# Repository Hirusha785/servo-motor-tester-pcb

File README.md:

# 🔧 Servo Motor Tester PCB

A compact PCB design for testing and controlling hobby servo motors using a 555 timer-based PWM signal generator. This project is designed for electronics learning, servo testing, prototyping, and basic embedded hardware experimentation.

---

## 📌 Project Overview

The **Servo Motor Tester PCB** allows users to generate a variable PWM signal to test standard servo motors without needing a microcontroller such as Arduino or ESP32. The circuit is based on the **NE555 timer IC**, with a potentiometer used to adjust the servo position by varying the pulse width.

This PCB is useful for checking servo motor movement, validating servo wiring, testing power connections, and learning basic PWM control concepts.

---

## ✨ Features

- 🔧 NE555-based PWM signal generation  
- 🎚️ Potentiometer control for servo position adjustment  
- 🔌 Dedicated 3-pin servo output connector  
- ⚡ 6V DC input supply connector  
- 💡 Power indicator LED  
- 🧩 Compact PCB layout  
- 🛠️ Beginner-friendly through-hole component design  
- 📐 Designed using KiCad  

---

## 🧠 How It Works

Servo motors are controlled using a PWM signal. A typical hobby servo expects a pulse every 20 ms, where the pulse width determines the motor position.

Typical servo control range:

| Pulse Width | Servo Position |
|------------|----------------|
| ~1.0 ms | 0° |
| ~1.5 ms | 90° |
| ~2.0 ms | 180° |

In this circuit, the **NE555 timer** works as an adjustable pulse generator. The potentiometer changes the timing resistance, which changes the output pulse width. This output signal is sent to the servo motor through the signal pin.

---

## 🧾 Components Used

| Reference | Component | Value / Type |
|----------|-----------|--------------|
| U1 | Timer IC | NE555P |
| RV1 | Potentiometer | 100kΩ |
| R1 | Resistor | 3.3kΩ |
| R2 | Resistor | 56kΩ |
| R3 | Resistor | 1kΩ |
| C1 | Capacitor | 22nF |
| D1 | Diode | 1N4148 |
| D2 | LED | Power Indicator |
| J1 | Power Connector | 2-pin input |
| J2 | Servo Connector | 3-pin output |

---

## 🔌 Pin Connections

### Power Input - J1

| Pin | Function |
|-----|----------|
| 1 | +6V DC |
| 2 | GND |

### Servo Output - J2

| Pin | Function |
|-----|----------|
| 1 | Signal |
| 2 | VCC |
| 3 | GND |

> ⚠️ Always verify the servo motor pinout before connecting. Different servo brands may use different wire color arrangements.

---
## 🖼️ Project Photos

### 1. Schematic Diagram

This schematic shows the NE555 timer-based PWM circuit, power input section, LED indicator, timing components, potentiometer, and servo output connector.

---

### 2. PCB Layout

This image shows the final routed PCB layout with component placement, traces, copper fill, connectors, mounting holes, and silkscreen labels.

---

### 3. 3D  View

This 3D view shows the completed PCB design with all through-hole components, including the NE555 IC, potentiometer, resistors, diode, capacitor, LED, and connectors.

---

---
## ⚡ Power Supply

Recommended input supply:

```text
6V DC

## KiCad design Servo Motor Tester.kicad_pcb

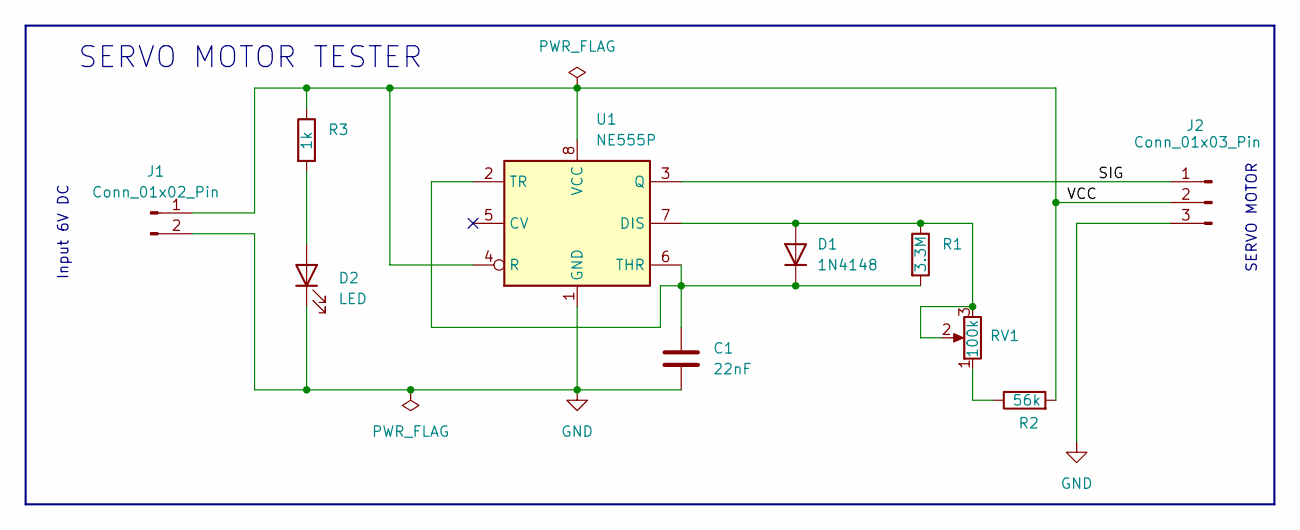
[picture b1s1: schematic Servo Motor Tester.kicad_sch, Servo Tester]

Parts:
C1: 22nF; C_Disc_D4.3mm_W1.9mm_P5.00mm
D1: 1N4148; D_DO-35_SOD27_P7.62mm_Horizontal
D2: LED; LED_Oval_W5.2mm_H3.8mm
J1: Conn_01x02_Pin; PinHeader_1x02_P2.54mm_Horizontal
J2: Conn_01x03_Pin; PinHeader_1x03_P2.54mm_Horizontal
R1: 3.3M; R_Axial_DIN0204_L3.6mm_D1.6mm_P5.08mm_Horizontal
R2: 56k; R_Axial_DIN0204_L3.6mm_D1.6mm_P7.62mm_Horizontal
R3: 1k; R_Axial_DIN0204_L3.6mm_D1.6mm_P7.62mm_Horizontal
RV1: 100k; Potentiometer_Alps_RK163_Single_Horizontal
U1: NE555P; DIP-8_W7.62mm

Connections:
/SIG: J2.1, U1.3 (Q)
/VCC: J1.1, J2.2, R2.2, R3.1, U1.4 (R), U1.8 (VCC)
GND: C1.2, D2.1 (K), J1.2, J2.3, U1.1 (GND)
unnamed: D1.2 (A), R1.1, RV1.2, RV1.3, U1.7 (DIS)
unnamed: C1.1, D1.1 (K), R1.2, U1.2 (TR), U1.6 (THR)
unnamed: D2.2 (A), R3.2
unnamed: R2.1, RV1.1

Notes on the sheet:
Input 6V DC
SERVO MOTOR
SERVO MOTOR TESTER

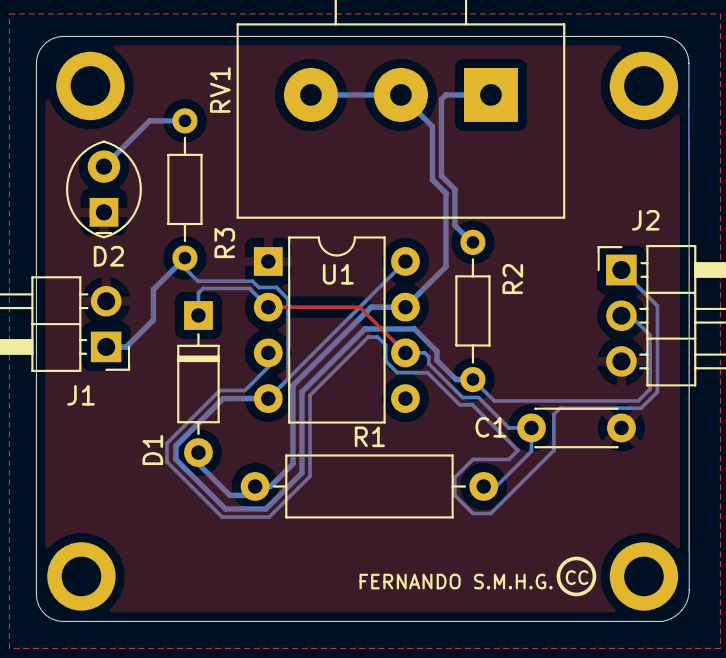
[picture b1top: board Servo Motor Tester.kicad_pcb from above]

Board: 2 copper layers, 36.3 x 32.5 mm, 10 parts (0 on the bottom side), 7 nets.
